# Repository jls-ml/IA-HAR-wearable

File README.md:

# IA-HAR-wearable

Wearable device project for Human Activity Recognition using Artificial Intelligence.

## Description

This project focuses on developing a wearable device capable of recognizing human activities using machine learning and artificial intelligence techniques.

## Project Structure

### Installation

```bash
# Clone the repository
git clone https://github.com/jls-ml/IA-HAR-wearable.git
cd IA-HAR-wearable
```

## Hardware

The hardware designs are located in the `hardware/` directory and include:
- Schematic files (.sch, .kicad_sch)
- PCB layouts (.kicad_pcb)
- Component libraries and footprints

## Contributing

Feel free to submit issues and enhancement requests!

## License

GNU General Public License v3.0

## Author

jls-ml

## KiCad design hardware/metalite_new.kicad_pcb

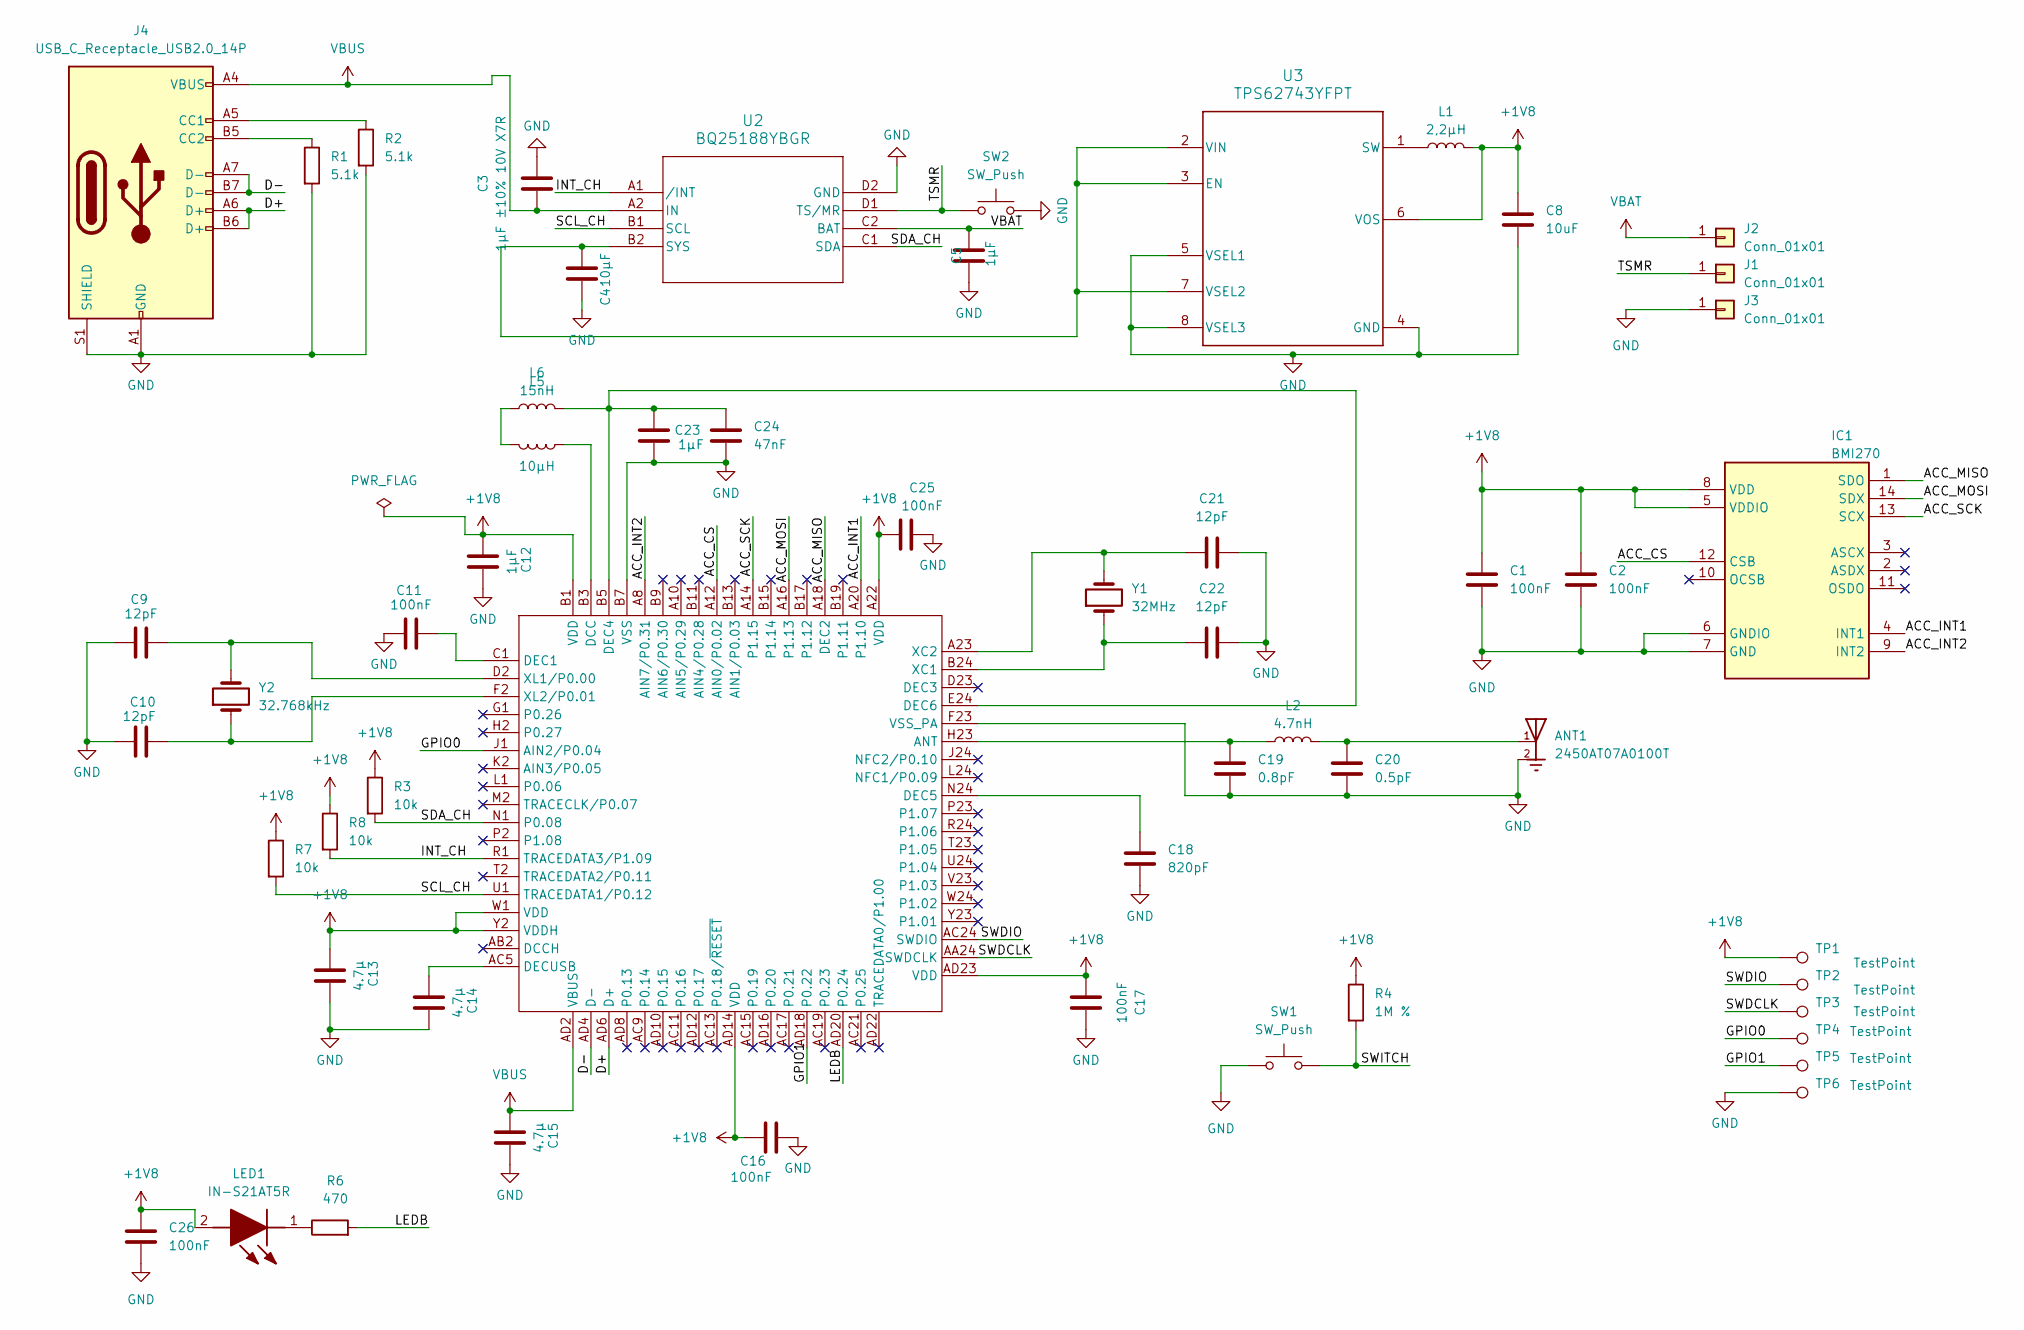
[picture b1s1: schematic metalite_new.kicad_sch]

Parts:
ANT1: 2450AT07A0100T; ANTENNA_2450AT07A0100T
C1, C2, C11, C16, C17, C25, C26: 100nF; C_0402_1005Metric
C3: 1µF ±10% 10V X7R; C_0603_1608Metric
C4: 10µF; C_0402_1005Metric
C5: 1µF; C_0402_1005Metric
C8: 10uF; C_0603_1608Metric
C9, C10, C21, C22: 12pF; C_0402_1005Metric
C12, C23: 1µF; C_0603_1608Metric
C13, C14, C15: 4.7µ; C_0603_1608Metric
C18: 820pF; C_0402_1005Metric
C19: 0.8pF; C_0402_1005Metric
C20: 0.5pF; C_0402_1005Metric
C24: 47nF; C_0402_1005Metric
IC1: BMI270; Mouser Part Number 262-BMI270
J1, J2, J3: Conn_01x01; SolderWire-0.1sqmm_1x01_D0.4mm_OD1mm
J4: USB_C_Receptacle_USB2.0_14P; USB_C_Receptacle_HRO_TYPE-C-31-M-12
L1: 2,2µH; L_0402_1005Metric
L2: 4.7nH; L_0402_1005Metric
L5: 10µH; L_0603_1608Metric
L6: 15nH; L_0402_1005Metric
LED1: IN-S21AT5R; INS21AT5R; Mouser Part Number 743-IN-S21AT5R
R1, R2: 5.1k; R_0402_1005Metric
R3, R7, R8: 10k; R_0402_1005Metric
R4: 1M %; C_0402_1005Metric
R6: 470; C_0402_1005Metric
SW1, SW2: SW_Push; PTS820J20KSMTRLFS
TP1, TP2, TP3, TP4, TP5, TP6: TestPoint; TestPoint_Pad_D1.0mm
U1: nRF52840; Nordic_AQFN-73-1EP_7x7mm_P0.5mm
U2: BQ25188YBGR; DSBGA8_YCK_TEX
U3: TPS62743YFPT; YFP0008-C01-IPC_A
Y1: 32MHz; CX2016FB32000D0FZZH1
Y2: 32.768kHz; Crystal_SMD_2012-2Pin_2.0x1.2mm_HandSoldering

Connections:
+1V8: C1.1, C2.1, C8.1, C12.1, C13.1, C16.1, C17.1, C25.1, C26.1, IC1.5 (VDDIO), IC1.8 (VDD), L1.2, LED1.2 (A), R3.1, R4.1, R7.1, R8.1, TP1.1, U1.A22 (VDD), U1.AD14 (VDD), U1.AD23 (VDD), U1.B1 (VDD), U1.W1 (VDD), U1.Y2 (VDDH), U3.6 (VOS)
/ACC_CS: IC1.12 (CSB), U1.A12 (AIN0/P0.02)
/ACC_INT1: IC1.4 (INT1), U1.A20 (P1.10)
/ACC_INT2: IC1.9 (INT2), U1.A8 (AIN7/P0.31)
/ACC_MISO: IC1.1 (SDO), U1.A18 (DEC2)
/ACC_MOSI: IC1.14 (SDX), U1.A16 (P1.13)
/ACC_SCK: IC1.13 (SCX), U1.A14 (P1.15)
/D+: J4.A6 (D+), J4.B6 (D+), U1.AD6 (D+)
/D-: J4.A7 (D-), J4.B7 (D-), U1.AD4 (D-)
/GPIO0: TP4.1, U1.J1 (AIN2/P0.04)
/GPIO1: TP5.1, U1.AD18 (P0.22)
/INT_CH: R8.2, U1.R1 (TRACEDATA3/P1.09), U2.A1 (/INT)
/LEDB: R6.2, U1.AD20 (P0.24)
/SCL_CH: R7.2, U1.U1 (TRACEDATA1/P0.12), U2.B1 (SCL)
/SDA_CH: R3.2, U1.N1 (P0.08), U2.C1 (SDA)
/SWDCLK: TP3.1, U1.AA24 (SWDCLK)
/SWDIO: TP2.1, U1.AC24 (SWDIO)
/SWITCH: R4.2, SW1.2
/TSMR: J1.1, SW2.1, U2.D1 (TS/MR)
GND: ANT1.2, ANT1.3, C1.2, C2.2, C3.2, C4.1, C5.1, C8.2, C9.1, C10.1, C11.1, C12.2, C13.2, C14.2, C15.2, C16.2, C17.2, C18.2, C19.2, C20.2, C21.2, C22.2, C23.2, C24.2, C25.2, C26.2, IC1.6 (GNDIO), IC1.7 (GND), J3.1, J4.A1 (GND), J4.A12 (GND), J4.B1 (GND), J4.B12 (GND), J4.S1 (SHIELD), R1.2, R2.2, SW1.1, SW2.2, TP6.1, U1.B7 (VSS), U1.F23 (VSS_PA), U2.D2 (GND), U3.4 (GND), U3.5 (VSEL1), U3.8 (VSEL3)
unnamed: ANT1.1, ANT1.4, C20.1, L2.2
unnamed: J4.A5 (CC1), R2.1
unnamed: J4.B5 (CC2), R1.1
unnamed: L5.2, L6.1
unnamed: LED1.1 (K), R6.1
unnamed: C19.1, L2.1, U1.H23 (ANT)
unnamed: L5.1, U1.B3 (DCC)
unnamed: C11.2, U1.C1 (DEC1)
unnamed: C23.1, C24.1, L6.2, U1.B5 (DEC4), U1.E24 (DEC6)
unnamed: C18.1, U1.N24 (DEC5)
unnamed: C14.1, U1.AC5 (DECUSB)
unnamed: C22.1, U1.B24 (XC1), Y1.1
unnamed: C21.1, U1.A23 (XC2), Y1.2
unnamed: C9.2, U1.D2 (XL1/P0.00), Y2.2
unnamed: C10.2, U1.F2 (XL2/P0.01), Y2.1
unnamed: C4.2, U2.B2 (SYS), U3.2 (VIN), U3.3 (EN), U3.7 (VSEL2)
unnamed: L1.1, U3.1 (SW)
VBAT: C5.2, J2.1, U2.C2 (BAT)
VBUS: C3.1, C15.1, J4.A4 (VBUS), J4.A9 (VBUS), J4.B4 (VBUS), J4.B9 (VBUS), U1.AD2 (VBUS), U2.A2 (IN)

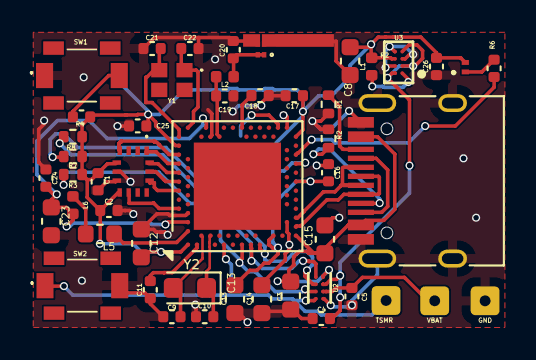
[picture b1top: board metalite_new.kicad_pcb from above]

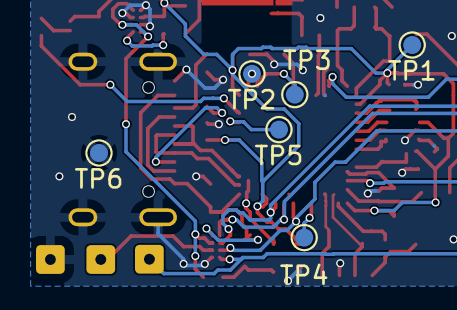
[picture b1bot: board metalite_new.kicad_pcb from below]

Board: 2 copper layers, 55 parts (6 on the bottom side), 39 nets.

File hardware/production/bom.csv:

Designator,Footprint,Quantity,Value,LCSC Part #
ANT1,ANTENNA_2450AT07A0100T,1,2450AT07A0100T,
"C1, C11, C16, C17, C2, C25, C26",0402,7,100nF,
"C10, C21, C22, C9",0402,4,12pF,
"C12, C23",0603,2,1µF,
"C13, C14, C15",0603,3,4.7µ,
C18,0402,1,820pF,
C19,0402,1,0.8pF,
C20,0402,1,0.5pF,
C24,0402,1,47nF,
C3,0603,1,1µF ±10% 10V X7R,
C4,0402,1,10µF,
C5,0402,1,1µF,
C8,0603,1,10uF,
IC1,BMI270,1,BMI270,
"J1, J2, J3",SolderWire-0.1sqmm_1x01_D0.4mm_OD1mm,3,Conn_01x01,
J4,USB_C_Receptacle_HRO_TYPE-C-31-M-12,1,USB_C_Receptacle_USB2.0_14P,
L1,0402,1,"2,2µH",
L2,0402,1,4.7nH,
L5,0603,1,10µH,
L6,0402,1,15nH,
LED1,INS21AT5R,1,IN-S21AT5R,
"R1, R2",0402,2,5.1k,
"R3, R7, R8",0402,3,10k,
R4,0402,1,1M  %,
R6,0402,1,470,
"SW1, SW2",PTS820J20KSMTRLFS,2,SW_Push,
"TP1, TP2, TP3, TP4, TP5, TP6",TestPoint_Pad_D1.0mm,6,TestPoint,
U1,Nordic_AQFN-73-1EP_7x7mm_P0.5mm,1,nRF52840,
U2,DSBGA8_YCK_TEX,1,BQ25188YBGR,
U3,YFP0008-C01-IPC_A,1,TPS62743YFPT,
Y1,CX2016FB32000D0FZZH1,1,32MHz,
Y2,Crystal_SMD_2012-2Pin_2.0x1.2mm_HandSoldering,1,32.768kHz,

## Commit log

2026-06-04 Initial commit: Add README.md
2026-06-04 Revise README for clarity and license information
    Updated project structure and installation instructions in README.
2026-06-04 Licencing
    ctrl+v
2026-06-05 Add KiCad hardware designs
